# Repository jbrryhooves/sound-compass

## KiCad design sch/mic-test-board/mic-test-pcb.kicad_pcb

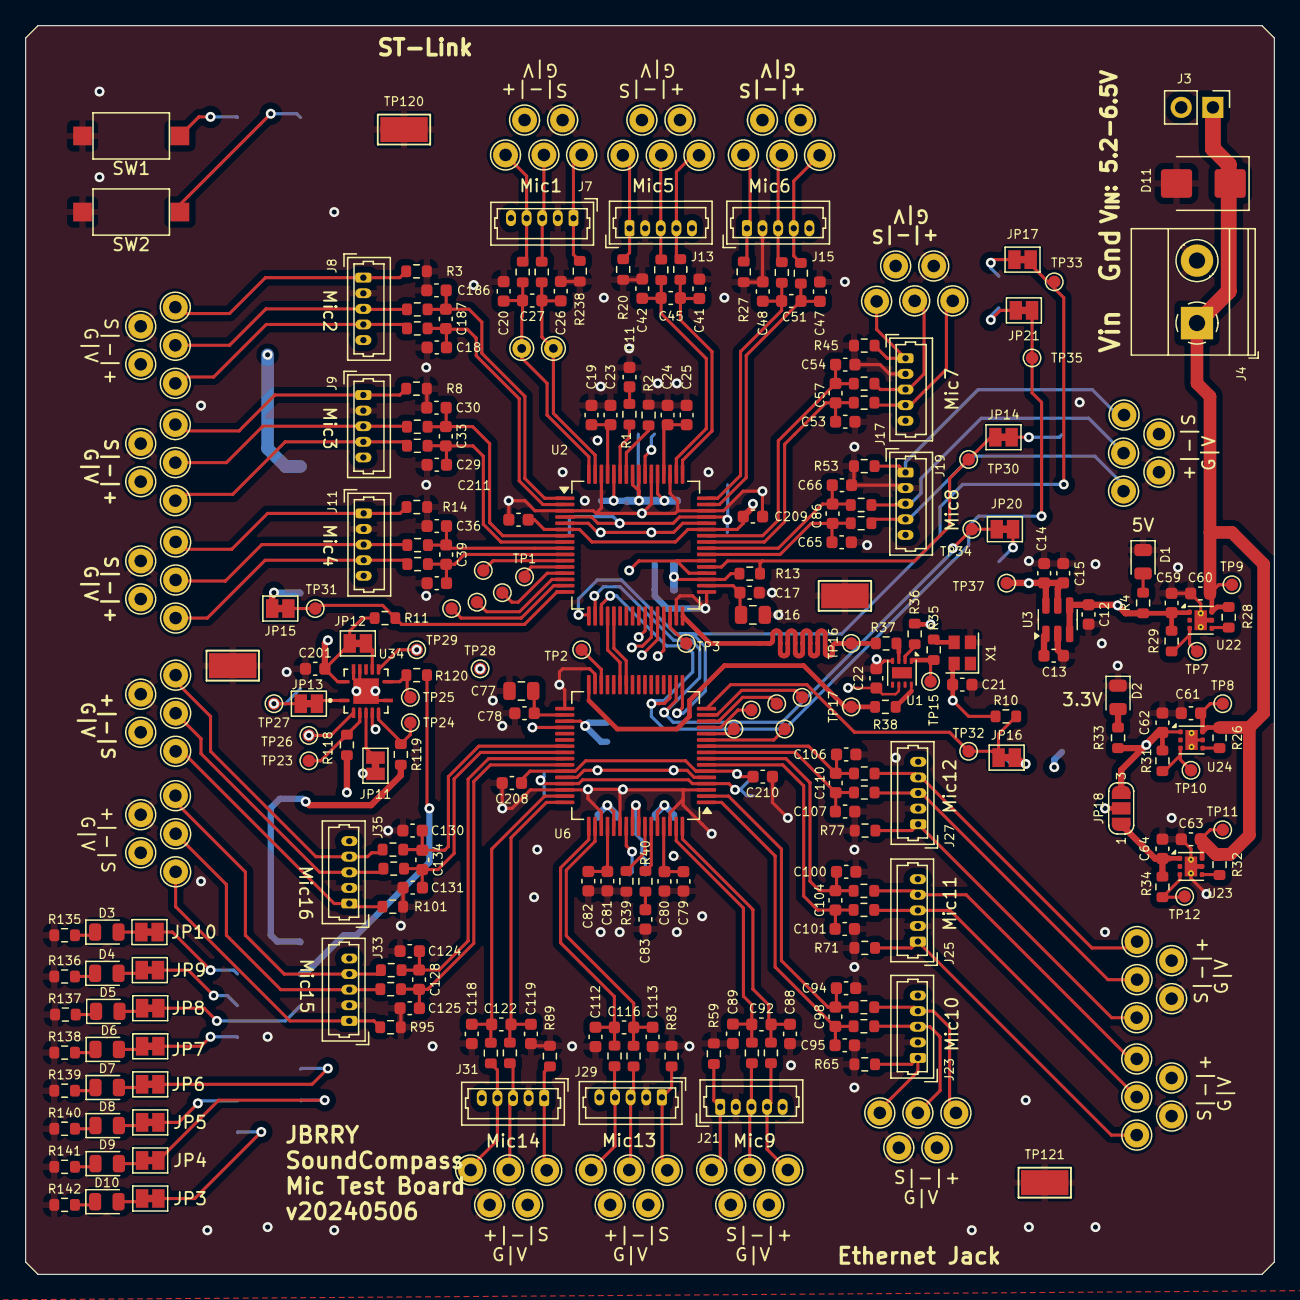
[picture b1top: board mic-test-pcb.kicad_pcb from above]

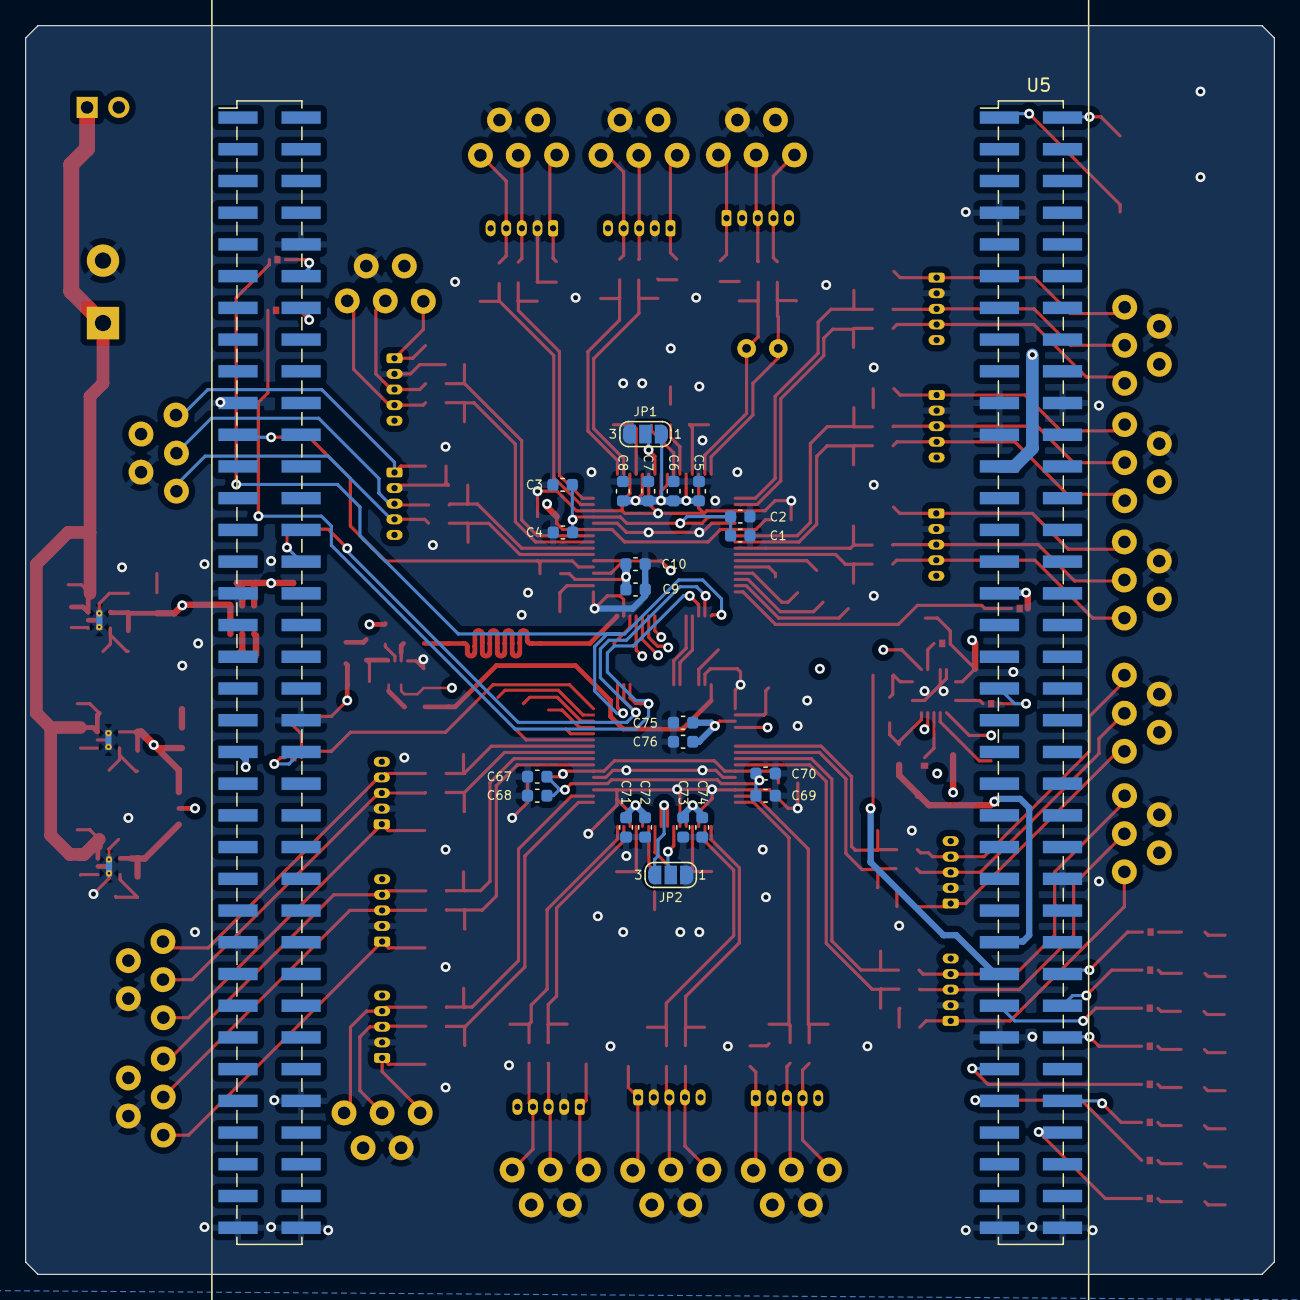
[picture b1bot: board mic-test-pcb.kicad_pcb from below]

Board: 4 copper layers, 100.0 x 100.0 mm, 359 parts (22 on the bottom side), 184 nets.

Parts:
C1, C3, C5, C7, C9, C12, C15, C19, C24, C59, C60, C61, C62, C63, C64, C67, C69, C71, C73, C75, C79, C81: 1uF; C_0603_1608Metric
C2, C4, C6, C8, C10, C11, C13, C14, C17, C21, C22, C23, C25, C68, C70, C72, C74, C76, C78, C80, C82, C83, C201, C208, C209, C210, C211: 0.1uF; C_0603_1608Metric
C16, C77: 10uF; C_0805_2012Metric
C18, C20, C26, C27, C29, C30, C33, C35, C36, C39, C41, C42, C45, C47, C48, C51, C53, C54, C57, C65, C66, C86, C88, C89, C92, C94, C95, C98, C100, C101, C104, C106, C107, C110, C112, C113, C116, C118, C119, C122, C124, C125, C128, C130, C131, C134, C186, C187: 10nF; C_0603_1608Metric
D1, D2, D3, D4, D5, D6, D7, D8, D9, D10: LED_Small_Filled; LED_0805_2012Metric
D11: SMBJ5340BE3/TR13; D_SMB
J3: Conn_01x03; PinHeader_1x02_P2.54mm_Vertical
J4: Conn_01x03; TerminalBlock_Phoenix_MKDS-1,5-2_1x02_P5.00mm_Horizontal
J7, J8, J9, J11, J13, J15, J17, J19, J21, J23, J25, J27, J29, J31, J33, J35: Conn_01x04; Molex_PicoBlade_53047-0510_1x05_P1.25mm_Vertical
JP1, JP2, JP18: SolderJumper_3_Open; SolderJumper-3_P1.3mm_Open_RoundedPad1.0x1.5mm_NumberLabels
JP3, JP4, JP5, JP6, JP7, JP8, JP9, JP10, JP11, JP12, JP13, JP14, JP15, JP16, JP17, JP20, JP21: SolderJumper_2_Bridged; SolderJumper-2_P1.3mm_Bridged_Pad1.0x1.5mm
R1, R40: 49.9R; R_0603_1608Metric
R2, R3, R8, R14, R20, R26, R27, R28, R32, R35, R37, R38, R39, R45, R53, R59, R65, R71, R77, R83, R89, R95, R101, R118, R119, R120, R238: 0R; R_0603_1608Metric
R4, R33, R135, R136, R137, R138, R139, R140, R141, R142: 470R; R_0603_1608Metric
R5, R6, R7, R9, R12, R15, R18, R21, R24, R30, R43, R46, R49, R54, R57, R60, R63, R66, R69, R72, R75, R78, R81, R84, R87, R90, R93, R96, R99, R102, R105, R223: 33R; R_0603_1608Metric
R10, R11, R13, R29, R31, R34, R36: 100k; R_0603_1608Metric
SW1, SW2: SW_Push; SW_SPST_CK_RS282G05A3
TP1, TP2, TP3, TP5, TP6, TP7, TP8, TP9, TP10, TP11, TP12, TP13, TP14, TP15, TP16, TP17, TP18, TP19, TP20, TP21, TP22, TP23, TP24, TP25, TP26, TP27, TP28, TP29, TP30, TP31, TP32, TP33, TP34, TP35, TP37: TestPoint; TestPoint_Pad_D1.0mm
TP4, TP36: Hole_1.5mm; TestPoint_THTPad_D1.5mm_Drill0.7mm
TP38, TP39, TP40, TP41, TP42, TP43, TP44, TP45, TP46, TP47, TP48, TP49, TP50, TP51, TP52, TP53, TP54, TP55, TP56, TP57, TP58, TP59, TP60, TP61, TP62, TP63, TP64, TP65, TP66, TP67, TP68, TP69, TP70, TP71, TP72, TP73, TP74, TP75, TP76, TP77, TP78, TP79, TP80, TP81, TP82, TP83, TP84, TP85, TP86, TP87, TP88, TP89, TP90, TP91, TP92, TP93, TP94, TP95, TP96, TP97, TP98, TP99, TP100, TP101, TP102, TP103, TP104, TP105, TP106, TP107, TP108, TP109, TP110, TP111, TP112, TP113, TP114, TP115, TP116, TP117: Hole_1.5mm; TestPoint_THTPad_D2.0mm_Drill1.0mm
TP118: 5019; TestPoint_Keystone_5019_Minature
TP119, TP120, TP121: Hole_1.5mm; TestPoint_Keystone_5019_Minature
U1: LMK1C1102; WSON-8-1EP_2x2mm_P0.5mm_EP0.9x1.6mm
U2, U6: AD7768BSTZ; LQFP-64_10x10mm_P0.5mm
U3: MAX6070BAUT33+T; SOT-23-6
U5: NUCLEO144-H743ZI; ST_Morpho_Connector_144_STLink_SMD_Headers_BottomMount
U22: LP5912-5.0DRV; WSON-6-1EP_2x2mm_P0.65mm_EP1x1.6mm_ThermalVias
U23, U24: LP5912-3.3DRV; WSON-6-1EP_2x2mm_P0.65mm_EP1x1.6mm_ThermalVias
U34: SN74LVC126ARGYR; IC_SN74AUC08RGYRG4
X1: KC3225Z32.7680C1KX00; Oscillator_SMD_SeikoEpson_SG210-4Pin_2.5x2.0mm

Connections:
+3.3V: C5.1, C6.1, C7.1, C8.1, C9.1, C10.1, C21.1, C22.1, C62.1, C71.1, C72.1, C73.1, C74.1, C75.1, C76.1, C201.1, JP1.3 (B), JP2.3 (B), JP11.1 (A), JP12.1 (A), JP18.3 (B), R10.2, R11.2, R13.2, R31.2, R33.1, R36.2, U1.6 (VCC), U2.35 (IOVDD), U2.53 (AVDD2B), U2.56 (FORMAT0), U2.57 (~PIN/SPI), U2.60 (AVDD2A), U6.35 (IOVDD), U6.53 (AVDD2B), U6.56 (FORMAT0), U6.57 (~PIN/SPI), U6.60 (AVDD2A), U24.1 (OUT), U34.14 (VCC), X1.4 (Vcc)
+3.3VA: J7.5, J8.5, J9.5, J11.5, J13.5, J15.5, J17.5, J19.5, J21.5, J23.5, J25.5, J27.5, J29.5, J31.5, J33.5, J35.5, JP18.2 (C), TP38.1, TP40.1, TP42.1, TP44.1, TP46.1, TP48.1, TP50.1, TP52.1, TP54.1, TP56.1, TP58.1, TP60.1, TP62.1, TP64.1, TP66.1, TP68.1
+5VA: C1.1, C2.1, C3.1, C4.1, C12.1, C59.1, C67.1, C68.1, C69.1, C70.1, R4.1, R29.2, U2.4 (AVDD1A), U2.45 (AVDD1B), U3.3 (EN), U3.4 (IN), U6.4 (AVDD1A), U6.45 (AVDD1B), U22.1 (OUT)
/ADC1 AD7768/AIN0+: C20.2, C27.1, R7.2, TP4.1, U2.64 (AIN0+)
/ADC1 AD7768/AIN0-: C26.1, C27.2, R223.2, TP36.1, U2.63 (AIN0-)
/ADC1 AD7768/AIN1+: C18.2, C187.1, R5.2, U2.2 (AIN1+)
/ADC1 AD7768/AIN1-: C186.1, C187.2, R6.2, U2.1 (AIN1-)
/ADC1 AD7768/AIN2+: C29.2, C33.1, R9.2, U2.8 (AIN2+)
/ADC1 AD7768/AIN2-: C30.1, C33.2, R12.2, U2.7 (AIN2-)
/ADC1 AD7768/AIN3+: C35.2, C39.1, R15.2, U2.10 (AIN3+)
/ADC1 AD7768/AIN3-: C36.1, C39.2, R18.2, U2.9 (AIN3-)
/ADC1 AD7768/AIN4+: C41.2, C45.1, R21.2, U2.49 (AIN4+)
/ADC1 AD7768/AIN4-: C42.1, C45.2, R24.2, U2.50 (AIN4-)
/ADC1 AD7768/AIN5+: C47.2, C51.1, R30.2, U2.47 (AIN5+)
/ADC1 AD7768/AIN5-: C48.1, C51.2, R43.2, U2.48 (AIN5-)
/ADC1 AD7768/AIN6+: C53.2, C57.1, R46.2, U2.41 (AIN6+)
/ADC1 AD7768/AIN6-: C54.1, C57.2, R49.2, U2.42 (AIN6-)
/ADC1 AD7768/AIN7+: C65.2, C86.1, R54.2, U2.39 (AIN7+)
/ADC1 AD7768/AIN7-: C66.1, C86.2, R57.2, U2.40 (AIN7-)
/ADC1 AD7768/DCLK: TP26.1, U2.28 (DCLK), U34.2 (A1)
/ADC1 AD7768/DOUT0: TP28.1, U2.27 (DOUT0), U34.5 (A2)
/ADC1 AD7768/DOUT1: TP29.1, U2.26 (DOUT1), U34.9 (A3)
/ADC1 AD7768/DOUT6: U2.21 (DOUT6), U6.26 (DOUT1)
/ADC1 AD7768/DOUT7: U2.20 (DOUT7), U6.27 (DOUT0)
/ADC1 AD7768/DREGCAP: C16.1, C17.1, U2.34 (DREGCAP)
/ADC1 AD7768/REGCAPA: C19.1, C23.1, U2.61 (REGCAPA)
/ADC1 AD7768/REGCAPB: C24.1, C25.1, U2.52 (REGCAPB)
/ADC1 AD7768/V_{OCM}: C11.1, R1.2
/ADC1 AD7768/~START: JP14.1 (A), R13.1, TP30.1, U2.37 (~START)
/ADC1 AD7768/~SYNC_IN: U2.36 (~SYNC_IN), U2.38 (~SYNC_OUT), U6.36 (~SYNC_IN)
/ADC2 AD7769/AIN0+: C88.2, C92.1, R60.2, U6.64 (AIN0+)
/ADC2 AD7769/AIN0-: C89.1, C92.2, R63.2, U6.63 (AIN0-)
/ADC2 AD7769/AIN1+: C94.2, C98.1, R66.2, U6.2 (AIN1+)
/ADC2 AD7769/AIN1-: C95.1, C98.2, R69.2, U6.1 (AIN1-)
/ADC2 AD7769/AIN2+: C100.2, C104.1, R72.2, U6.8 (AIN2+)
/ADC2 AD7769/AIN2-: C101.1, C104.2, R75.2, U6.7 (AIN2-)
/ADC2 AD7769/AIN3+: C106.2, C110.1, R78.2, U6.10 (AIN3+)
/ADC2 AD7769/AIN3-: C107.1, C110.2, R81.2, U6.9 (AIN3-)
/ADC2 AD7769/AIN4+: C112.2, C116.1, R84.2, U6.49 (AIN4+)
/ADC2 AD7769/AIN4-: C113.1, C116.2, R87.2, U6.50 (AIN4-)
/ADC2 AD7769/AIN5+: C118.2, C122.1, R90.2, U6.47 (AIN5+)
/ADC2 AD7769/AIN5-: C119.1, C122.2, R93.2, U6.48 (AIN5-)
/ADC2 AD7769/AIN6+: C124.2, C128.1, R96.2, U6.41 (AIN6+)
/ADC2 AD7769/AIN6-: C125.1, C128.2, R99.2, U6.42 (AIN6-)
/ADC2 AD7769/AIN7+: C130.2, C134.1, R102.2, U6.39 (AIN7+)
/ADC2 AD7769/AIN7-: C131.1, C134.2, R105.2, U6.40 (AIN7-)
/ADC2 AD7769/DREGCAP: C77.1, C78.1, U6.34 (DREGCAP)
/ADC2 AD7769/REGCAPA: C79.1, C80.1, U6.61 (REGCAPA)
/ADC2 AD7769/REGCAPB: C81.1, C82.1, U6.52 (REGCAPB)
/ADC2 AD7769/V_{OCM}: C83.1, R40.2
/DRDY: JP13.1 (A), TP27.1, U2.29 (~DRDY), U5.38 (PC0)
/MCLK_1: R37.2, TP16.1, U2.32 (XTAL2/MCLK)
/MCLK_2: R38.2, TP17.1, U6.32 (XTAL2/MCLK)
/SPI1_MISO: JP21.1 (A), TP35.1, U2.19 (DEC0/SDO), U6.19 (DEC0/SDO)
/SPI1_MOSI: JP20.1 (A), TP34.1, U2.18 (DEC1/SDI), U6.18 (DEC1/SDI)
/SPI1_SCLK: JP17.1 (A), TP33.1, U2.17 (ST1/SCLK), U6.17 (ST1/SCLK)
/SPI1_~CS1: JP15.1 (A), R11.1, TP31.1, U2.16 (ST0/~CS)
/SPI1_~CS2: JP16.1 (A), R10.1, TP32.1, U6.16 (ST0/~CS)
/V_{IN}: C60.1, C61.1, C63.1, D11.1 (K), J3.1, J4.1, R26.1, R28.1, R32.1, TP8.1, TP9.1, TP11.1, U22.6 (IN), U23.6 (IN), U24.6 (IN)
/V_{REF}: C14.1, C15.1, C208.1, C209.1, C210.1, C211.1, TP37.1, U2.6 (REF1+), U2.43 (REF2+), U3.5 (OUTS), U3.6 (OUTF), U6.6 (REF1+), U6.43 (REF2+)
/uController/GPIO_~START_uC: JP14.2 (B), U5.94 (PB2)
/uController/LED1: D10.2 (A), JP3.2 (B)
/uController/LED1_uC: JP3.1 (A), U5.65 (PG12)
/uController/LED2: D9.2 (A), JP4.2 (B)
/uController/LED2_uC: JP4.1 (A), U5.64 (PG15)
/uController/LED3: D8.2 (A), JP5.2 (B)
/uController/LED3_uC: JP5.1 (A), U5.63 (PG9)
/uController/LED4: D7.2 (A), JP6.2 (B)
/uController/LED4_uC: JP6.1 (A), U5.62 (PE6)
/uController/LED5: D6.2 (A), JP7.2 (B)
/uController/LED5_uC: JP7.1 (A), U5.59 (PG0)
/uController/LED6: D5.2 (A), JP8.2 (B)
/uController/LED6_uC: JP8.1 (A), U5.58 (PG1)
/uController/LED7: D4.2 (A), JP9.2 (B)
/uController/LED7_uC: JP9.1 (A), U5.57 (PD0)
/uController/LED8: D3.2 (A), JP10.2 (B)
/uController/LED8_uC: JP10.1 (A), U5.55 (PD1)
/uController/SPI1_MISO_uC: JP21.2 (B), U5.85 (PA6)
/uController/SPI1_MOSI_uC: JP20.2 (B), U5.101 (PB5)
/uController/SPI1_SCLK_uC: JP17.2 (B), U5.83 (PA5)
/uController/SPI1_~CS1_uC: JP15.2 (B), U5.32 (PA4)
/uController/SPI1_~CS2_uC: JP16.2 (B), U5.113 (PD13)
/uController/SPI2_MOSI1_buff: R119.2, U5.54 (PF8)
/uController/SPI2_MOSI2_buff: R120.2, U5.56 (PF9)
/uController/SPI2_SCLK_buff: R118.2, U5.114 (PF10)
/uController/V_{IN}: J3.2, U5.24 (VIN)
/uController/~PButton1: SW1.1, U5.1 (PC10)
/uController/~PButton2: SW2.1, U5.2 (PC11)
GND: C1.2, C2.2, C3.2, C4.2, C5.2, C6.2, C7.2, C8.2, C9.2, C10.2, C11.2, C12.2, C13.2, C14.2, C15.2, C16.2, C17.2, C18.1, C19.2, C20.1, C21.2, C22.2, C23.2, C24.2, C25.2, C26.2, C29.1, C30.2, C35.1, C36.2, C41.1, C42.2, C47.1, C48.2, C53.1, C54.2, C59.2, C60.2, C61.2, C62.2, C63.2, C64.2, C65.1, C66.2, C67.2, C68.2, C69.2, C70.2, C71.2, C72.2, C73.2, C74.2, C75.2, C76.2, C77.2, C78.2, C79.2, C80.2, C81.2, C82.2, C83.2, C88.1, C89.2, C94.1, C95.2, C100.1, C101.2, C106.1, C107.2, C112.1, C113.2, C118.1, C119.2, C124.1, C125.2, C130.1, C131.2, C186.2, C201.2, C208.2, C209.2, C210.2, C211.2, D1.1 (K), D2.1 (K), D11.2 (A), J4.2, J7.2, J8.2, J9.2, J11.2, J13.2, J15.2, J17.2, J19.2, J21.2, J23.2, J25.2, J27.2, J29.2, J31.2, J33.2, J35.2, JP1.1 (A), JP2.1 (A), R2.1, R3.1, R8.1, R14.1, R20.1, R27.1, R39.1, R45.1, R53.1, R59.1, R65.1, R71.1, R77.1, R83.1, R89.1, R95.1, R101.1, R135.2, R136.2, R137.2, R138.2, R139.2, R140.2, R141.2, R142.2, R238.1, SW1.2, SW2.2, TP86.1, TP87.1, TP88.1, TP89.1, TP90.1, TP91.1, TP92.1, TP93.1, TP94.1, TP95.1, TP96.1, TP97.1, TP98.1, TP99.1, TP100.1, TP101.1, TP118.1, TP119.1, TP120.1, TP121.1, U1.4 (GND), U2.3 (AVSS1A), U2.5 (REF1-), U2.31 (XTAL1), U2.33 (DGND), U2.44 (REF2-), U2.46 (AVSS1B), U2.51 (AVSS2B), U2.54 (AVSS), U2.62 (AVSS2A), U3.2 (GND), U5.8 (GND), U5.19 (GND), U5.20 (GND), U5.22 (GND), U5.49 (GND), U5.60 (GND), U5.71 (GND), U5.72 (GND), U5.81 (GND), U5.92 (GND), U5.104 (AGND), U5.111 (GND), U5.126 (GND), U5.135 (GND), U5.143 (GND), U5.144 (GND), U6.3 (AVSS1A), U6.5 (REF1-), U6.31 (XTAL1), U6.33 (DGND), U6.44 (REF2-), U6.46 (AVSS1B), U6.51 (AVSS2B), U6.54 (AVSS), U6.62 (AVSS2A), U22.5 (GND), U22.7 (EP), U23.5 (GND), U23.7 (EP), U24.5 (GND), U24.7 (EP), U34.7 (GND), U34.12 (A4), U34.13, U34.15 (EP), X1.2 (GND)
unnamed: D1.2 (A), R4.2
unnamed: D2.2 (A), R33.2
unnamed: D3.1 (K), R135.1
unnamed: D4.1 (K), R136.1
unnamed: D5.1 (K), R137.1
unnamed: D6.1 (K), R138.1
unnamed: D7.1 (K), R139.1
unnamed: D8.1 (K), R140.1
unnamed: D9.1 (K), R141.1
unnamed: D10.1 (K), R142.1
unnamed: J7.1, R238.2, TP103.1
unnamed: J7.3, R223.1, TP71.1
unnamed: J7.4, R7.1, TP41.1
unnamed: J8.1, R3.2, TP106.1
unnamed: J8.3, R6.1, TP74.1
unnamed: J8.4, R5.1, TP47.1
unnamed: J9.1, R8.2, TP102.1
unnamed: J9.3, R12.1, TP70.1
unnamed: J9.4, R9.1, TP39.1
unnamed: J11.1, R14.2, TP104.1
unnamed: J11.3, R18.1, TP72.1
unnamed: J11.4, R15.1, TP43.1
unnamed: J13.1, R20.2, TP105.1
unnamed: J13.3, R24.1, TP73.1
unnamed: J13.4, R21.1, TP45.1
unnamed: J15.1, R27.2, TP107.1
unnamed: J15.3, R43.1, TP75.1
unnamed: J15.4, R30.1, TP49.1
unnamed: J17.1, R45.2, TP108.1
unnamed: J17.3, R49.1, TP76.1
unnamed: J17.4, R46.1, TP51.1
unnamed: J19.1, R53.2, TP109.1
unnamed: J19.3, R57.1, TP77.1
unnamed: J19.4, R54.1, TP53.1
unnamed: J21.1, R59.2, TP110.1
unnamed: J21.3, R63.1, TP78.1
unnamed: J21.4, R60.1, TP55.1
unnamed: J23.1, R65.2, TP111.1
unnamed: J23.3, R69.1, TP79.1
unnamed: J23.4, R66.1, TP57.1
unnamed: J25.1, R71.2, TP112.1
unnamed: J25.3, R75.1, TP80.1
unnamed: J25.4, R72.1, TP59.1
unnamed: J27.1, R77.2, TP113.1
unnamed: J27.3, R81.1, TP81.1
unnamed: J27.4, R78.1, TP61.1
unnamed: J29.1, R83.2, TP114.1
unnamed: J29.3, R87.1, TP82.1
unnamed: J29.4, R84.1, TP63.1
unnamed: J31.1, R89.2, TP115.1
unnamed: J31.3, R93.1, TP83.1
unnamed: J31.4, R90.1, TP65.1
unnamed: J33.1, R95.2, TP116.1
unnamed: J33.3, R99.1, TP84.1
unnamed: J33.4, R96.1, TP67.1
unnamed: J35.1, R101.2, TP117.1
unnamed: J35.3, R105.1, TP85.1
unnamed: J35.4, R102.1, TP69.1
unnamed: JP1.2 (C), U2.55 (FORMAT1)
unnamed: JP2.2 (C), U6.55 (FORMAT1)
unnamed: JP11.2 (B), U34.4
unnamed: JP12.2 (B), U34.10
unnamed: JP13.2 (B), U34.1
unnamed: C64.1, JP18.1 (A), R34.2, U23.1 (OUT)
unnamed: R118.1, TP23.1, U34.3
unnamed: R119.1, TP24.1, U34.6
unnamed: R120.1, TP25.1, U34.8
unnamed: R36.1, U1.2 (1G/Enable)
unnamed: R35.2, TP15.1, U1.1 (CLKIN)
unnamed: R37.1, U1.3 (Y0)
unnamed: R38.1, U1.8 (Y1)
unnamed: R2.2, U2.58 (CLK_SEL)
unnamed: TP14.1, U2.11 (FILTER/GPIO4)
unnamed: TP1.1, U2.12 (MODE0/GPIO0)
unnamed: TP5.1, U2.13 (MODE1/GPIO1)
unnamed: TP6.1, U2.14 (MODE2/GPIO2)
unnamed: TP13.1, U2.15 (MODE3/GPIO3)
unnamed: R1.1, U2.59 (VCM)
unnamed: TP3.1, U2.30 (~RESET)
unnamed: C13.1, U3.1 (FILTER)
unnamed: R39.2, U6.58 (CLK_SEL)
unnamed: TP22.1, U6.11 (FILTER/GPIO4)
unnamed: TP18.1, U6.12 (MODE0/GPIO0)
unnamed: TP19.1, U6.13 (MODE1/GPIO1)
unnamed: TP20.1, U6.14 (MODE2/GPIO2)
unnamed: TP21.1, U6.15 (MODE3/GPIO3)
unnamed: R40.1, U6.59 (VCM)
unnamed: TP2.1, U6.30 (~RESET)
unnamed: R28.2, U22.4 (EN)
unnamed: R29.1, TP7.1, U22.3 (PG)
unnamed: R32.2, U23.4 (EN)
unnamed: R34.1, TP12.1, U23.3 (PG)
unnamed: R26.2, U24.4 (EN)
unnamed: R31.1, TP10.1, U24.3 (PG)
unnamed: R35.1, X1.3 (OUT)

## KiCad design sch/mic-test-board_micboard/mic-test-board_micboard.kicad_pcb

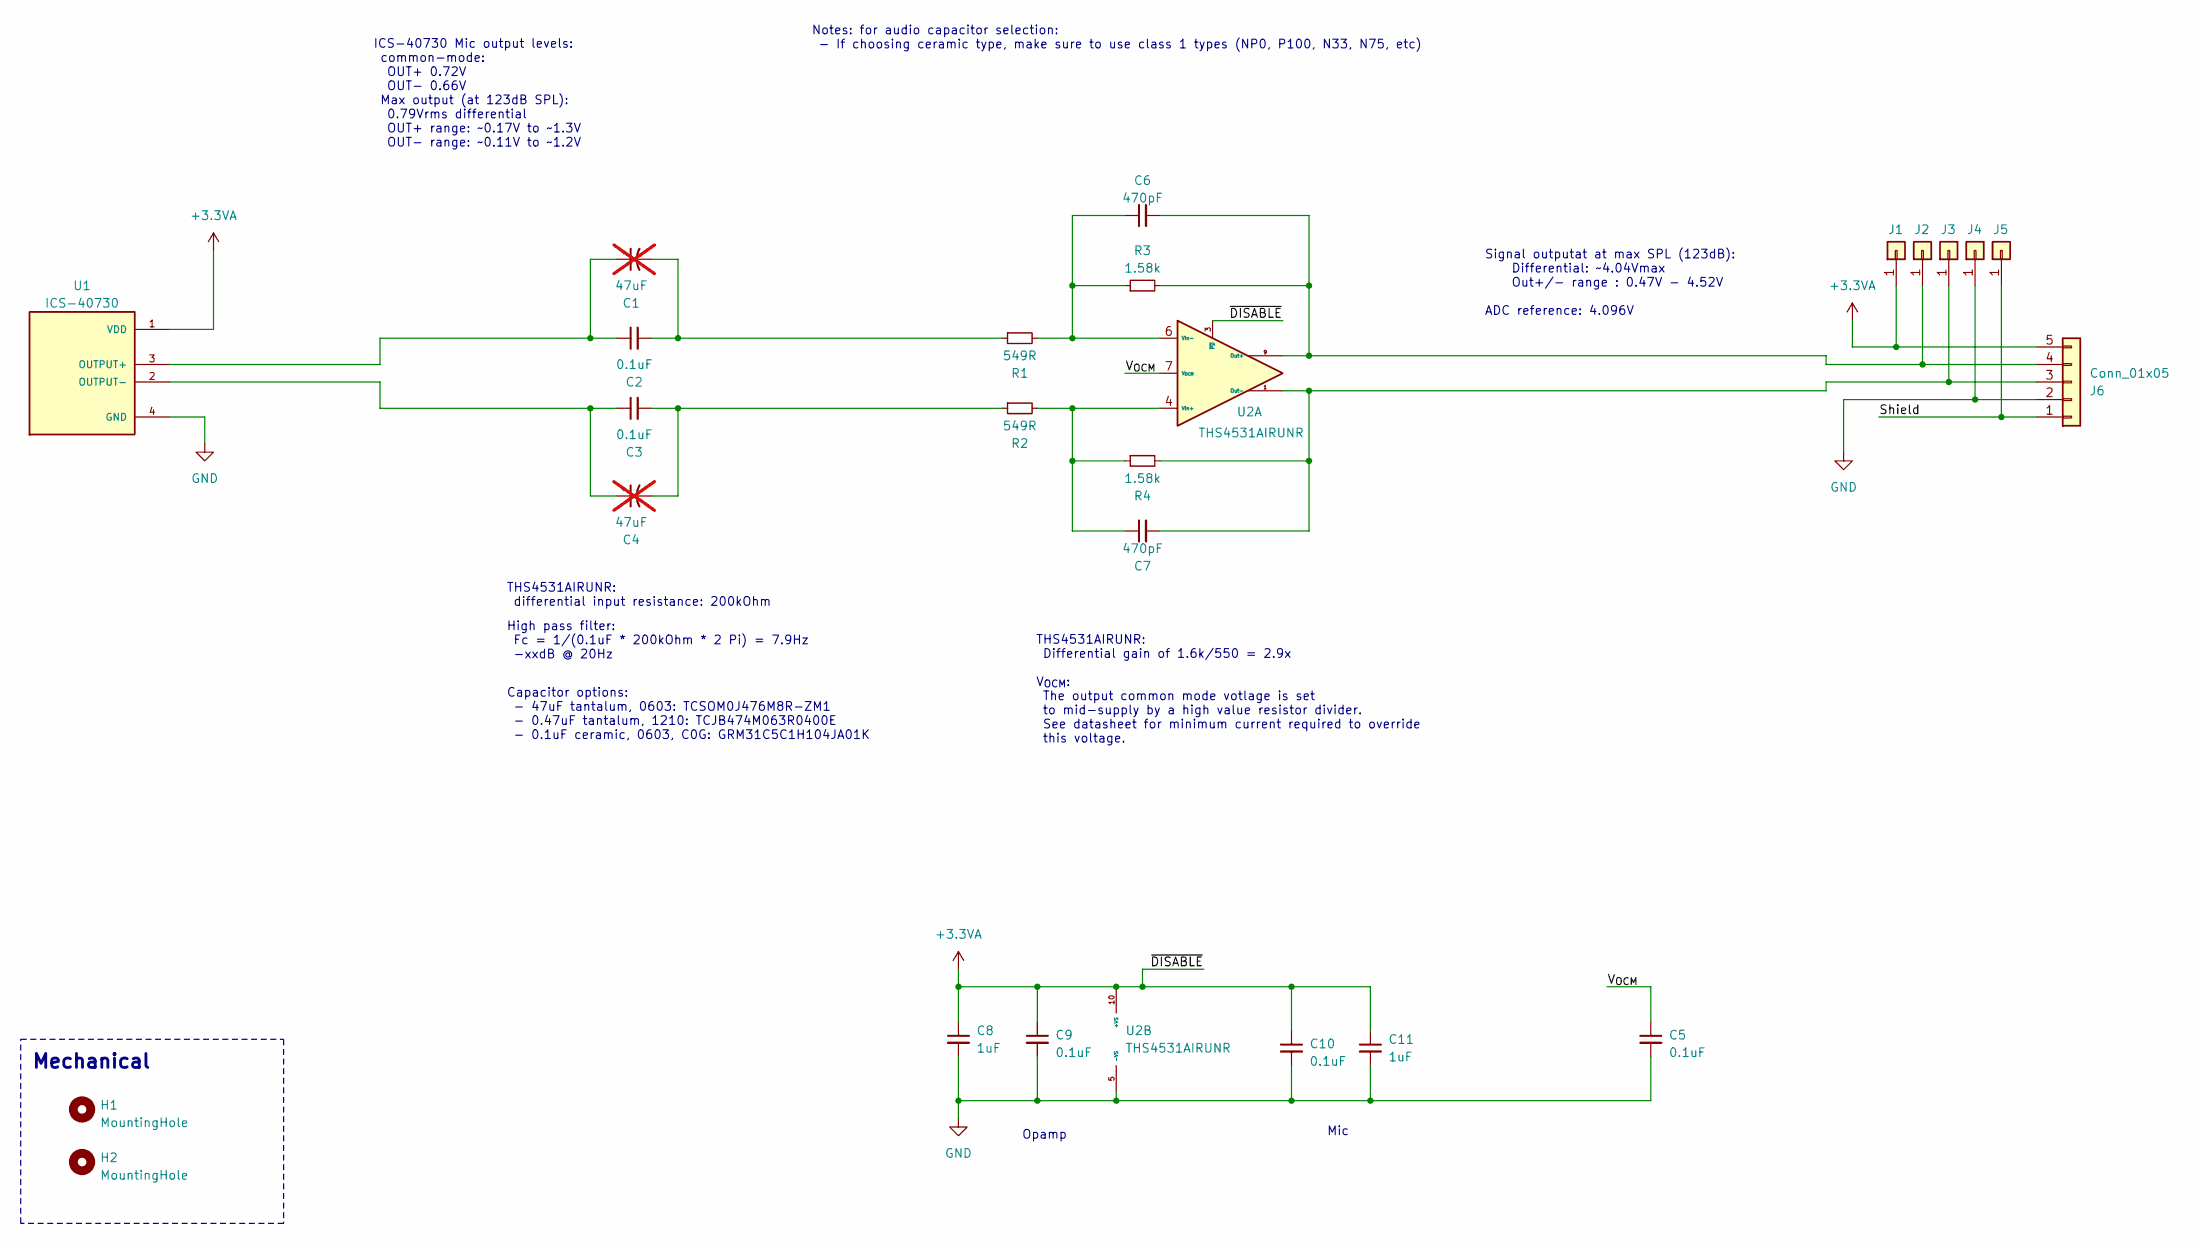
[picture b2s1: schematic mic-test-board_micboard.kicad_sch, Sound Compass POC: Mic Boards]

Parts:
C1, C4: 47uF; CP_EIA-1608-08_AVX-J; Part Number TCSOM0J476M8R-ZM1; not fitted
C2, C3: 0.1uF; C_1206_3216Metric; Voltage 50V; Part Number GRM31C5C1H104JA01K
C5, C9, C10: 0.1uF; C_0603_1608Metric; Part Number C0603C104K8RAC7867
C6, C7: 470pF; C_0603_1608Metric; Part Number 885012006027
C8, C11: 1uF; C_0603_1608Metric; Part Number CL10B105KP8NNNC
H1: MountingHole; MountingHole_3.2mm_M3; Part Number R30-1003002
H2: MountingHole; MountingHole_2.2mm_M2; Part Number R30-1003002
J1, J2, J3, J4, J5: Conn_01x01; TestPoint_THTPad_D2.0mm_Drill1.0mm
J6: Conn_01x05; Molex_PicoBlade_53047-0510_1x05_P1.25mm_Vertical; Part Number 0530470510
R1, R2: 549R; R_0603_1608Metric; Part Number RC0603FR-07549RL
R3, R4: 1.58k; R_0603_1608Metric; Part Number RC0603FR-071K58L
U1: ICS-40730; MIC_ICS-40730; Part Number ICS-40730
U2: THS4531AIRUNR; Texas_RUN0010A_WQFN-10_2x2mm_P0.5mm; Part Number THS4531AIRUNR

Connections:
+3.3VA: C8.1, C9.1, C10.1, C11.1, J1.1, J6.5, U1.1 (VDD), U2.3 (~PD), U2.10 (+VS)
/Shield: J5.1, J6.1
/V_{OCM}: C5.1, U2.7 (V_{OCM})
GND: C5.2, C8.2, C9.2, C10.2, C11.2, J4.1, J6.2, U1.4 (GND), U2.5 (-VS)
unnamed: C1.2, C2.2, R1.1
unnamed: C3.2, C4.2, R2.1
unnamed: C6.2, J2.1, J6.4, R3.2, U2.9 (Out+)
unnamed: C7.2, J3.1, J6.3, R4.2, U2.1 (Out-)
unnamed: C1.1, C2.1, U1.3 (OUTPUT+)
unnamed: C3.1, C4.1, U1.2 (OUTPUT-)
unnamed: C6.1, R1.2, R3.1, U2.6 (VIn-)
unnamed: C7.1, R2.2, R4.1, U2.4 (Vin+)

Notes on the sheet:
High pass filter: Fc = 1/(0.1uF * 200kOhm * 2 Pi) = 7.9Hz -xxdB @ 20Hz
THS4531AIRUNR: differential input resistance: 200kOhm
Notes: for audio capacitor selection: - If choosing ceramic type, make sure to use class 1 types (NP0, P100, N33, N75, etc)
THS4531AIRUNR: Differential gain of 1.6k/550 = 2.9x V_{OCM}: The output common mode votlage is set to mid-supply by a high value resistor divider. See datasheet for minimum current required to override this voltage.
Signal outputat at max SPL (123dB): Differential: ~4.04Vmax Out+/- range : 0.47V - 4.52V ADC reference: 4.096V
Mic
Opamp
ICS-40730 Mic output levels: common-mode: OUT+ 0.72V OUT- 0.66V Max output (at 123dB SPL): 0.79Vrms differential OUT+ range: ~0.17V to ~1.3V OUT- range: ~0.11V to ~1.2V
Mechanical
Capacitor options: - 47uF tantalum, 0603: TCSOM0J476M8R-ZM1 - 0.47uF tantalum, 1210: TCJB474M063R0400E - 0.1uF ceramic, 0603, C0G: GRM31C5C1H104JA01K

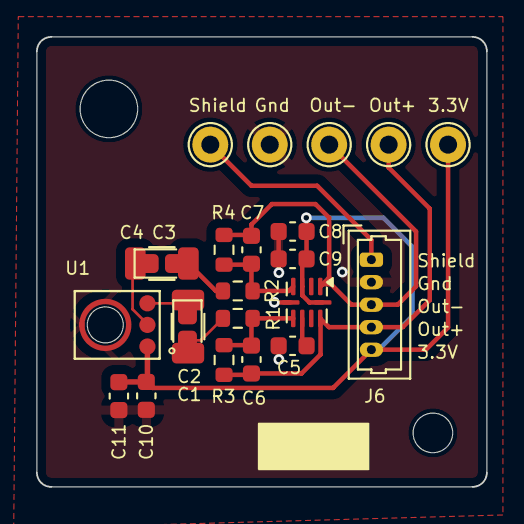
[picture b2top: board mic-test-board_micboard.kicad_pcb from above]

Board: 2 copper layers, 25.0 x 25.0 mm, 25 parts (0 on the bottom side), 12 nets.

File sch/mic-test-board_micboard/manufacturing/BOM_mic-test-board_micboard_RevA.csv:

Reference,Value,Datasheet,Footprint,Qty,Extended,Extra,Total,DNP,${EXCLUDE_FROM_BOM},Manufacturer,Part Number,Supplier,Supplier Number
C1 C4,47uF,~,Capacitor_Tantalum_SMD:CP_EIA-1608-08_AVX-J,2,32,,32,DNP,,KYOCERA AVX,TCSOM0J476M8R-ZM1,Digi-Key,478-TCSOM0J476M8R-ZM1CT-ND
C2 C3,0.1uF,~,Capacitor_SMD:C_1206_3216Metric,2,32,,32,,,Murata Electronics,GRM31C5C1H104JA01K,Digi-Key,490-8335-1-ND
C5 C9 C10,0.1uF,~,Capacitor_SMD:C_0603_1608Metric,3,48,,48,,,KEMET,C0603C104K8RAC7867,Digi-Key,399-C0603C104K8RAC7867CT-ND
C6 C7,470pF,~,Capacitor_SMD:C_0603_1608Metric,2,32,,32,,,Würth Elektronik,8.85012E+11,Digi-Key,732-7770-1-ND
C8 C11,1uF,~,Capacitor_SMD:C_0603_1608Metric,2,32,,32,,,Samsung Electro-Mechanics,CL10B105KP8NNNC,Digi-Key,1276-1946-1-ND
H1 H2,MountingHole,~,-- mixed values --,2,32,,32,,,Harwin Inc.,R30-1003002,Digi-Key,952-2610-ND
J6,Conn_01x05,https://www.molex.com/pdm_docs/sd/530470510_sd.pdf,Connector_Molex:Molex_PicoBlade_53047-0510_1x05_P1.25mm_Vertical,1,16,,16,,,Molex,0530470510,Digi-Key,WM1734-ND
R1 R2,549R,~,Resistor_SMD:R_0603_1608Metric,2,32,,32,,,YAGEO,RC0603FR-07549RL,Digi-Key,311-549HRCT-ND
R3 R4,1.58k,~,Resistor_SMD:R_0603_1608Metric,2,32,,32,,,YAGEO,RC0603FR-071K58L,Digi-Key,311-1.58KHRCT-ND
U1,ICS-40730,https://invensense.tdk.com/wp-content/uploads/2020/07/DS-000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,mic-test-board:MIC_ICS-40730,1,16,,16,,,TDK InvenSense,ICS-40730,Digi-Key,1428-1141-1-ND
U2,THS4531AIRUNR,https://www.ti.com/lit/ds/symlink/ths4531a.pdf,Package_DFN_QFN:Texas_RUN0010A_WQFN-10_2x2mm_P0.5mm,1,16,,16,,,Texas Instruments,THS4531AIRUNR,Digi-Key,296-THS4531AIRUNRCT-ND
,,,,,,,,,,,,,
,,,,,,,,,,,,,
,,,,,,,,,,,,,
,,,,,,,,,,,,,
,,,,,,,,,,,,,
Number of Boards,16,,,,,,,,,,,,

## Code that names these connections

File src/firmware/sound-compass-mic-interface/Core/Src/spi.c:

/* USER CODE BEGIN Header */
/**
  ******************************************************************************
  * @file    spi.c
  * @brief   This file provides code for the configuration
  *          of the SPI instances.
  ******************************************************************************
  * @attention
  *
  * Copyright (c) 2024 STMicroelectronics.
  * All rights reserved.
  *
  * This software is licensed under terms that can be found in the LICENSE file
  * in the root directory of this software component.
  * If no LICENSE file comes with this software, it is provided AS-IS.
  *
  ******************************************************************************
  */
/* USER CODE END Header */
/* Includes ------------------------------------------------------------------*/
#include "spi.h"

/* USER CODE BEGIN 0 */

/* USER CODE END 0 */

SPI_HandleTypeDef hspi1;
DMA_HandleTypeDef hdma_spi1_rx;
DMA_HandleTypeDef hdma_spi1_tx;

/* SPI1 init function */
void MX_SPI1_Init(void)
{

  /* USER CODE BEGIN SPI1_Init 0 */

  /* USER CODE END SPI1_Init 0 */

  /* USER CODE BEGIN SPI1_Init 1 */

  /* USER CODE END SPI1_Init 1 */
  hspi1.Instance = SPI1;
  hspi1.Init.Mode = SPI_MODE_MASTER;
  hspi1.Init.Direction = SPI_DIRECTION_2LINES;
  hspi1.Init.DataSize = SPI_DATASIZE_8BIT;
  hspi1.Init.CLKPolarity = SPI_POLARITY_LOW;
  hspi1.Init.CLKPhase = SPI_PHASE_1EDGE;
  hspi1.Init.NSS = SPI_NSS_SOFT;
  hspi1.Init.BaudRatePrescaler = SPI_BAUDRATEPRESCALER_32;
  hspi1.Init.FirstBit = SPI_FIRSTBIT_MSB;
  hspi1.Init.TIMode = SPI_TIMODE_DISABLE;
  hspi1.Init.CRCCalculation = SPI_CRCCALCULATION_DISABLE;
  hspi1.Init.CRCPolynomial = 0x0;
  hspi1.Init.NSSPMode = SPI_NSS_PULSE_ENABLE;
  hspi1.Init.NSSPolarity = SPI_NSS_POLARITY_LOW;
  hspi1.Init.FifoThreshold = SPI_FIFO_THRESHOLD_01DATA;
  hspi1.Init.TxCRCInitializationPattern = SPI_CRC_INITIALIZATION_ALL_ZERO_PATTERN;
  hspi1.Init.RxCRCInitializationPattern = SPI_CRC_INITIALIZATION_ALL_ZERO_PATTERN;
  hspi1.Init.MasterSSIdleness = SPI_MASTER_SS_IDLENESS_00CYCLE;
  hspi1.Init.MasterInterDataIdleness = SPI_MASTER_INTERDATA_IDLENESS_00CYCLE;
  hspi1.Init.MasterReceiverAutoSusp = SPI_MASTER_RX_AUTOSUSP_DISABLE;
  hspi1.Init.MasterKeepIOState = SPI_MASTER_KEEP_IO_STATE_DISABLE;
  hspi1.Init.IOSwap = SPI_IO_SWAP_DISABLE;
  if (HAL_SPI_Init(&hspi1) != HAL_OK)
  {
    Error_Handler();
  }
  /* USER CODE BEGIN SPI1_Init 2 */

  /* USER CODE END SPI1_Init 2 */

}

void HAL_SPI_MspInit(SPI_HandleTypeDef* spiHandle)
{

  GPIO_InitTypeDef GPIO_InitStruct = {0};
  RCC_PeriphCLKInitTypeDef PeriphClkInitStruct = {0};
  if(spiHandle->Instance==SPI1)
  {
  /* USER CODE BEGIN SPI1_MspInit 0 */

  /* USER CODE END SPI1_MspInit 0 */

  /** Initializes the peripherals clock
  */
    PeriphClkInitStruct.PeriphClockSelection = RCC_PERIPHCLK_SPI1;
    PeriphClkInitStruct.PLL3.PLL3M = 32;
    PeriphClkInitStruct.PLL3.PLL3N = 98;
    PeriphClkInitStruct.PLL3.PLL3P = 4;
    PeriphClkInitStruct.PLL3.PLL3Q = 2;
    PeriphClkInitStruct.PLL3.PLL3R = 2;
    PeriphClkInitStruct.PLL3.PLL3RGE = RCC_PLL3VCIRANGE_1;
    PeriphClkInitStruct.PLL3.PLL3VCOSEL = RCC_PLL3VCOWIDE;
    PeriphClkInitStruct.PLL3.PLL3FRACN = 0;
    PeriphClkInitStruct.Spi123ClockSelection = RCC_SPI123CLKSOURCE_PLL3;
    if (HAL_RCCEx_PeriphCLKConfig(&PeriphClkInitStruct) != HAL_OK)
    {
      Error_Handler();
    }

    /* SPI1 clock enable */
    __HAL_RCC_SPI1_CLK_ENABLE();

    __HAL_RCC_GPIOA_CLK_ENABLE();
    __HAL_RCC_GPIOB_CLK_ENABLE();
    /**SPI1 GPIO Configuration
    PA5     ------> SPI1_SCK
    PA6     ------> SPI1_MISO
    PB5     ------> SPI1_MOSI
    */
    GPIO_InitStruct.Pin = GPIO_PIN_5|GPIO_PIN_6;
    GPIO_InitStruct.Mode = GPIO_MODE_AF_PP;
    GPIO_InitStruct.Pull = GPIO_NOPULL;
    GPIO_InitStruct.Speed = GPIO_SPEED_FREQ_VERY_HIGH;
    GPIO_InitStruct.Alternate = GPIO_AF5_SPI1;
    HAL_GPIO_Init(GPIOA, &GPIO_InitStruct);

    GPIO_InitStruct.Pin = GPIO_PIN_5;
    GPIO_InitStruct.Mode = GPIO_MODE_AF_PP;
    GPIO_InitStruct.Pull = GPIO_NOPULL;
    GPIO_InitStruct.Speed = GPIO_SPEED_FREQ_VERY_HIGH;
    GPIO_InitStruct.Alternate = GPIO_AF5_SPI1;
    HAL_GPIO_Init(GPIOB, &GPIO_InitStruct);

    /* SPI1 DMA Init */
    /* SPI1_RX Init */
    hdma_spi1_rx.Instance = DMA1_Stream0;
    hdma_spi1_rx.Init.Request = DMA_REQUEST_SPI1_RX;
    hdma_spi1_rx.Init.Direction = DMA_PERIPH_TO_MEMORY;
    hdma_spi1_rx.Init.PeriphInc = DMA_PINC_DISABLE;
    hdma_spi1_rx.Init.MemInc = DMA_MINC_ENABLE;
    hdma_spi1_rx.Init.PeriphDataAlignment = DMA_PDATAALIGN_BYTE;
    hdma_spi1_rx.Init.MemDataAlignment = DMA_MDATAALIGN_BYTE;
    hdma_spi1_rx.Init.Mode = DMA_CIRCULAR;
    hdma_spi1_rx.Init.Priority = DMA_PRIORITY_HIGH;
    hdma_spi1_rx.Init.FIFOMode = DMA_FIFOMODE_DISABLE;
    if (HAL_DMA_Init(&hdma_spi1_rx) != HAL_OK)
    {
      Error_Handler();
    }

    __HAL_LINKDMA(spiHandle,hdmarx,hdma_spi1_rx);

    /* SPI1_TX Init */
    hdma_spi1_tx.Instance = DMA1_Stream1;
    hdma_spi1_tx.Init.Request = DMA_REQUEST_SPI1_TX;
    hdma_spi1_tx.Init.Direction = DMA_MEMORY_TO_PERIPH;
    hdma_spi1_tx.Init.PeriphInc = DMA_PINC_DISABLE;
    hdma_spi1_tx.Init.MemInc = DMA_MINC_ENABLE;
    hdma_spi1_tx.Init.PeriphDataAlignment = DMA_PDATAALIGN_BYTE;
    hdma_spi1_tx.Init.MemDataAlignment = DMA_MDATAALIGN_BYTE;
    hdma_spi1_tx.Init.Mode = DMA_CIRCULAR;
    hdma_spi1_tx.Init.Priority = DMA_PRIORITY_LOW;
    hdma_spi1_tx.Init.FIFOMode = DMA_FIFOMODE_DISABLE;
    if (HAL_DMA_Init(&hdma_spi1_tx) != HAL_OK)
    {
      Error_Handler();
    }

    __HAL_LINKDMA(spiHandle,hdmatx,hdma_spi1_tx);

    /* SPI1 interrupt Init */
    HAL_NVIC_SetPriority(SPI1_IRQn, 5, 0);
    HAL_NVIC_EnableIRQ(SPI1_IRQn);
  /* USER CODE BEGIN SPI1_MspInit 1 */

  /* USER CODE END SPI1_MspInit 1 */
  }
}

void HAL_SPI_MspDeInit(SPI_HandleTypeDef* spiHandle)
{

  if(spiHandle->Instance==SPI1)
  {
  /* USER CODE BEGIN SPI1_MspDeInit 0 */

  /* USER CODE END SPI1_MspDeInit 0 */
    /* Peripheral clock disable */
    __HAL_RCC_SPI1_CLK_DISABLE();

    /**SPI1 GPIO Configuration
    PA5     ------> SPI1_SCK
    PA6     ------> SPI1_MISO
    PB5     ------> SPI1_MOSI
    */
    HAL_GPIO_DeInit(GPIOA, GPIO_PIN_5|GPIO_PIN_6);

    HAL_GPIO_DeInit(GPIOB, GPIO_PIN_5);

    /* SPI1 DMA DeInit */
    HAL_DMA_DeInit(spiHandle->hdmarx);
    HAL_DMA_DeInit(spiHandle->hdmatx);

    /* SPI1 interrupt Deinit */
    HAL_NVIC_DisableIRQ(SPI1_IRQn);
  /* USER CODE BEGIN SPI1_MspDeInit 1 */

  /* USER CODE END SPI1_MspDeInit 1 */
  }
}

/* USER CODE BEGIN 1 */

/* USER CODE END 1 */

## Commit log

2023-10-18 added some research scripts for generating Beam patterns, and 1/3 octave filter responses
    added C# program to generate microphone signals
2023-10-18 added start of firmware project. C++ blinky runs on dev board
2023-10-22 added first pass of diag class. Printf is not working yet
2023-10-23 added some colour and formatting to console out
2023-10-28 committing ETL state machine work for potential future reference before proceeding without it for now
2023-10-29 removed statemachine
2023-10-29 added task factory and second task.
2023-11-06 added ITimer, TimerFreeRTOS, and added timers to exec and audioprocessor
2023-11-06 bulk format. no code changes
2023-11-20 feat: performance enhancements
    - increased clock speed from 64MHz to 480MHz
    - Moved working buffers of IIR filter bank to DTCM
2023-11-26 added generation of 1/3 ocatve bands, and hardcoded them in.
    added mic position calculation
    added steering delay calculation
    added signal summing with shifting
    loop time for 20ms of signal, with beam steering, and 1/3 octave band filtering for steered beam and the 'centre' mic is ~15ms
2023-11-28 turned optimisation to -O3 and the loop time dropped to 8ms (from 15ms) for 1 beam, 30 filters.
2023-12-07 added start of a c++ project to process the 1/3 octave filters. Using the KFR library, clang in release mode, it can do 30 x 4th order IIR filters over 960 samples, for each of the 50 angles in ~5ms 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
2023-12-16 added thread pool library.
2024-02-06 added start of ethernet based STM32 pathway.
    - TCP server is running
2024-02-06 removed old STM32 project
2024-02-12 firmware feat: SPI -> ethernet basics working
    - SPI data is being written and read via DMA at the required bit rate
    - message queues are setup and working to send TCP data when SPI data arrives
    - some more buffering/slack needs to be introduced to allow for jittery TCP consumers applying back pressure
2024-03-01 doc: committing current state of block diagram before pivot to analog mic + ADC architecture
2024-03-04 feat: commiting ICS-52000 based mic test board before pivot to analog mic + ADC's
2024-03-14 feat: schematic WIP
    - Analog front end 99% selected and wired up
    - uController/dev board interface 1% done
2024-04-10 pcb: commit before large routing effort
    - schematic refactor to split preamps to each mic board
    - Mic board and main board are placed
    - no tracks laid
    - critical parts selected
2024-04-10 firmware: test code for streaming fake audio data over TCP
2024-05-05 pcb: finished routing mic board and ADC board.
    - BOM complete
    - uController pinout configured with CubeMX and re-checked
2024-05-08 pcb: ordered PCB's and BOM! RevA and v240506
2024-09-08 large updates: ADC pretty much working over SAI.
2024-09-13 added start of rust project
2024-09-13 firmware: sai working with one ADC, TCP server streaming (unconfirmed) data
2024-09-13 added python FIR based beamforming research and prototype
2025-03-21 sch: adding bringup notes
2025-03-21 doc: small changes to block diagrams
2025-03-21 src: large WIP commit for show and tell
2025-03-21 doc: added schematic and PCB pdf exports
2025-03-21 doc: added block diagram PDF export
2025-03-21 doc: missed a page of system block diagrams
